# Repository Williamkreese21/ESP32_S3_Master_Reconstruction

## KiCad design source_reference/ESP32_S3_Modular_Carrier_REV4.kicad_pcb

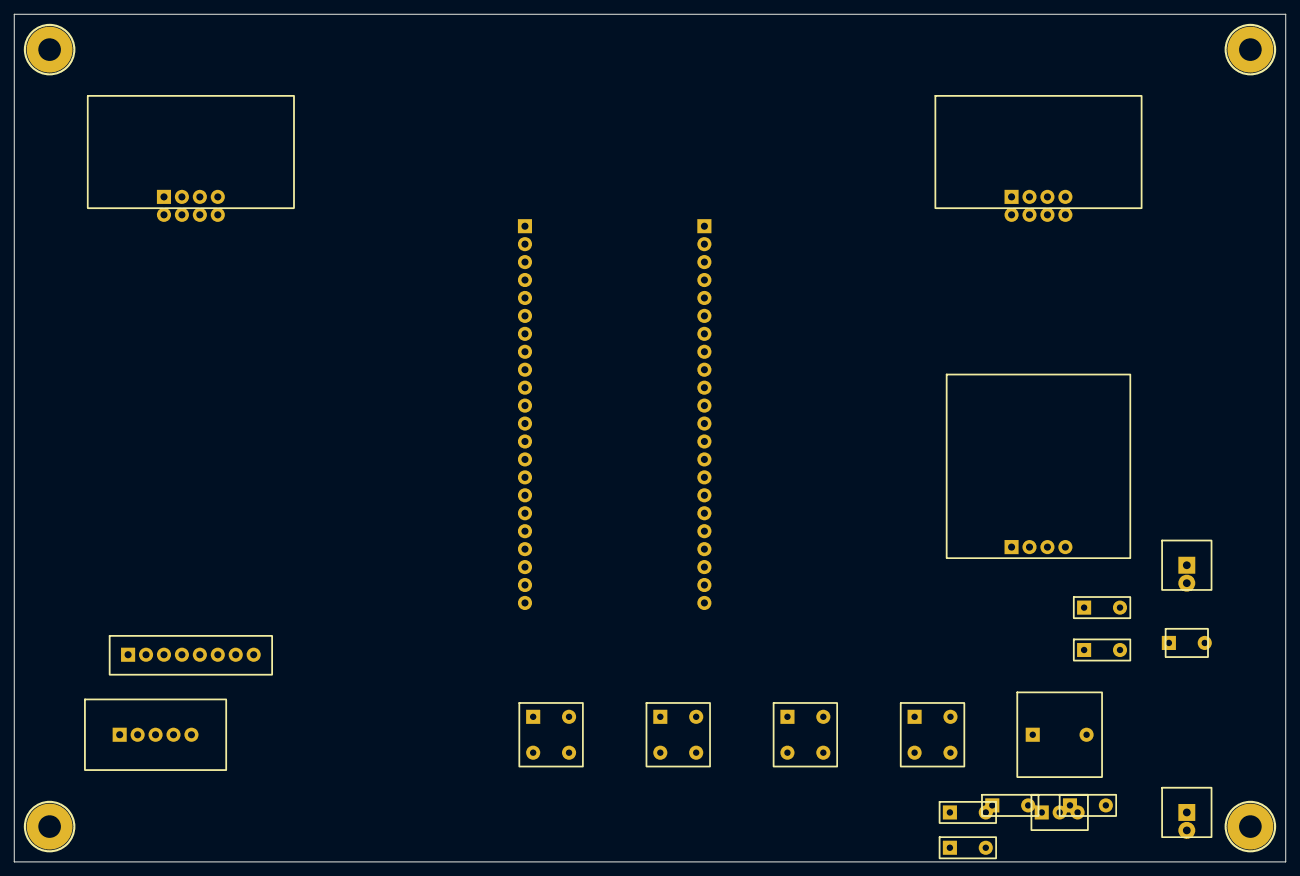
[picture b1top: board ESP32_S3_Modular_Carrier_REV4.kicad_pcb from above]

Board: 2 copper layers, 180.0 x 120.0 mm, 23 parts (0 on the bottom side), 31 nets, no tracks yet.

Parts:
BZ1: Active buzzer; BZ1
C8: 100nF; C8
D1: SS14; D1
F1: PTC 0.75A; F1
J1: ESP32-S3 DevKitC-1 1x22 socket; J1
J3: ESP32-S3 DevKitC-1 1x22 socket; J3
J_BAT: BATTERY SENSE; J_BAT
J_ENC1: KY-040 5P; J_ENC1
J_GPS1: NEO-6M GPS 4P; J_GPS1
J_PWR: 5V INPUT; J_PWR
J_RF1: nRF24L01+ 2x4 socket; J_RF1
J_RF2: nRF24L01+ 2x4 socket; J_RF2
J_TFT_BUS: TFT BUS 1x8 external; J_TFT_BUS
Q1: 2N3904 TO-92; Q1
R5: 1k; R5
R6: 100k; R6
R13: 2.2k; R13
R14: 1k; R14
SW1: 6x6 tactile; SW1
SW2: 6x6 tactile; SW2
SW3: 6x6 tactile; SW3
SW4: 6x6 tactile; SW4
U1_3D: ESP32-S3 DevKitC-1 N16R8; U1_3D

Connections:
3V3: BZ1.1, J1.1, J1.2, J_ENC1.2, J_GPS1.1, J_RF1.2, J_RF2.2, J_TFT_BUS.1, J_TFT_BUS.8
5V_FUSED: D1.1, F1.2
5V_IN: F1.1, J_PWR.1
5V_PROTECTED: D1.2, J1.21
BAT_ADC: C8.1, R13.2, R14.1
BUZZER_BASE: Q1.1, R5.2, R6.1
BUZZER_LOW: BZ1.2, Q1.2
GND: C8.2, J1.22, J3.1, J3.21, J3.22, J_BAT.2, J_ENC1.1, J_GPS1.2, J_PWR.2, J_RF1.1, J_RF1.8, J_RF2.1, J_RF2.8, J_TFT_BUS.2, Q1.3, R6.2, R14.2, SW1.3, SW1.4, SW2.3, SW2.4, SW3.3, SW3.4, SW4.3, SW4.4
GPIO1: J3.4, J_RF2.4
GPIO2: J3.5, J_RF2.3
GPIO3: J1.13, J_RF1.4
GPIO4: J1.4, J_RF1.3
GPIO5: J1.5, J_RF1.7, J_RF2.7
GPIO6: J1.6, J_RF1.5, J_RF2.5
GPIO7: J1.7, J_RF1.6, J_RF2.6
GPIO8: J1.12, J_TFT_BUS.7
GPIO9: J1.15, J_TFT_BUS.5
GPIO10: J1.16, J_TFT_BUS.6
GPIO11: J1.17, J_TFT_BUS.4
GPIO12: J1.18, J_TFT_BUS.3
GPIO13: J1.19, SW1.1, SW1.2
GPIO14: J1.20, SW2.1, SW2.2
GPIO15: J1.8, SW3.1, SW3.2
GPIO16: J1.9, SW4.1, SW4.2
GPIO17: J1.10, J_GPS1.4
GPIO18: J1.11, J_GPS1.3
GPIO39: J3.9, J_ENC1.3
GPIO40: J3.8, J_ENC1.4
GPIO41: J3.7, J_ENC1.5
GPIO42: J3.6, R5.1
VBAT_RAW: J_BAT.1, R13.1
